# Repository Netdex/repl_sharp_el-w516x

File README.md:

# repl_sharp_el-w516x
`This project is a work-in-progress.`

## Overview
repl_sharp_el-w516x is a design for a replacement logic board for the SHARP EL-W516X calculator.

## Design
The goal of this project is to create a more powerful/elegant calculator out of as many components from the original 
calculator as possible.

This design reuses all components of the calculator except the following:
- Solar panel
  - It does not deliver enough power regardless
- Display
  - Connector pitch is too fine, and flex cable is too fragile
  - There are about 100 pins on the connector, and it requires a application-specific driver
  - The display is replaced with the [NHD-C12832A1Z-FSW-FBW-3V3](http://www.newhavendisplay.com/specs/NHD-C12832A1Z-FSW-FBW-3V3.pdf)
- PCB
- Battery
  - The original battery is an LR44 coin cell watch battery, which does not deliver the power required
  - The battery is replaced with a Samsung 3.8V Li-ion battery 

### Key matrix

The original calculator uses a carbon-coated silicone pad with carbon contacts on the PCB. This design uses the exact 
button pad footprint of the original calculator, with copper contacts instead.

The keys are arranged in a matrix, with a serial-in-parallel-out shift register on the rows, and a 
parallel-in-serial-out shift register on the columns. The microcontroller polls row and column pairs to detect 
key presses. Each column has a diode to avoid sinking 3V3 to GND when two buttons in the same row are pressed. 
In the case of multiple keys presed at once, ghosting will occur since diodes are only placed on a column-basis.

### Power delivery

The board is powered by a battery management IC with power path. The IC upregulates the battery voltage to +BATT + 250mV as VCC, 
where +BATT can vary from 3.0V (depleted) to 4.35V (full). An additional LDO regulates VCC to 3V3, which powers the 
microcontroller and other circuitry. The LDO has a dropout voltage of +250mV, which means that the battery will still 
have a bit of power left when it is depleted. The battery management IC actually charges to CV 4.2V, which means it 
will not charge the battery to full capacity (~80-90%).

The board can be charged via USB, which is also used for programming the microcontroller and other data transfer. 
Charging can occur while the device is being used, due to the power path management provided by the battery management 
IC. The battery charging current will automatically be ducked if the system power path draws too much power, to 
maintain system function. 

### uC
An ATMEGA32U4 microcontroller controls the display, input polling via shift registers, and computation. It is 
programmable via USB interface (factory ships with bootloader). ICSP is exposed via pads if required. 

Since the uC is powered by 3V3, an external 8 MHz oscillator provides the clock source.

## BOM
[InteractiveHtmlBom](https://raw.githack.com/Netdex/repl_sharp_el-w516x/master/kicad/bom/ibom.html)

## Pictures
3D Renders

Populated board (still covered in flux)

Front, in enclosure

Back, in enclosure (I need to file down the jagged edges)

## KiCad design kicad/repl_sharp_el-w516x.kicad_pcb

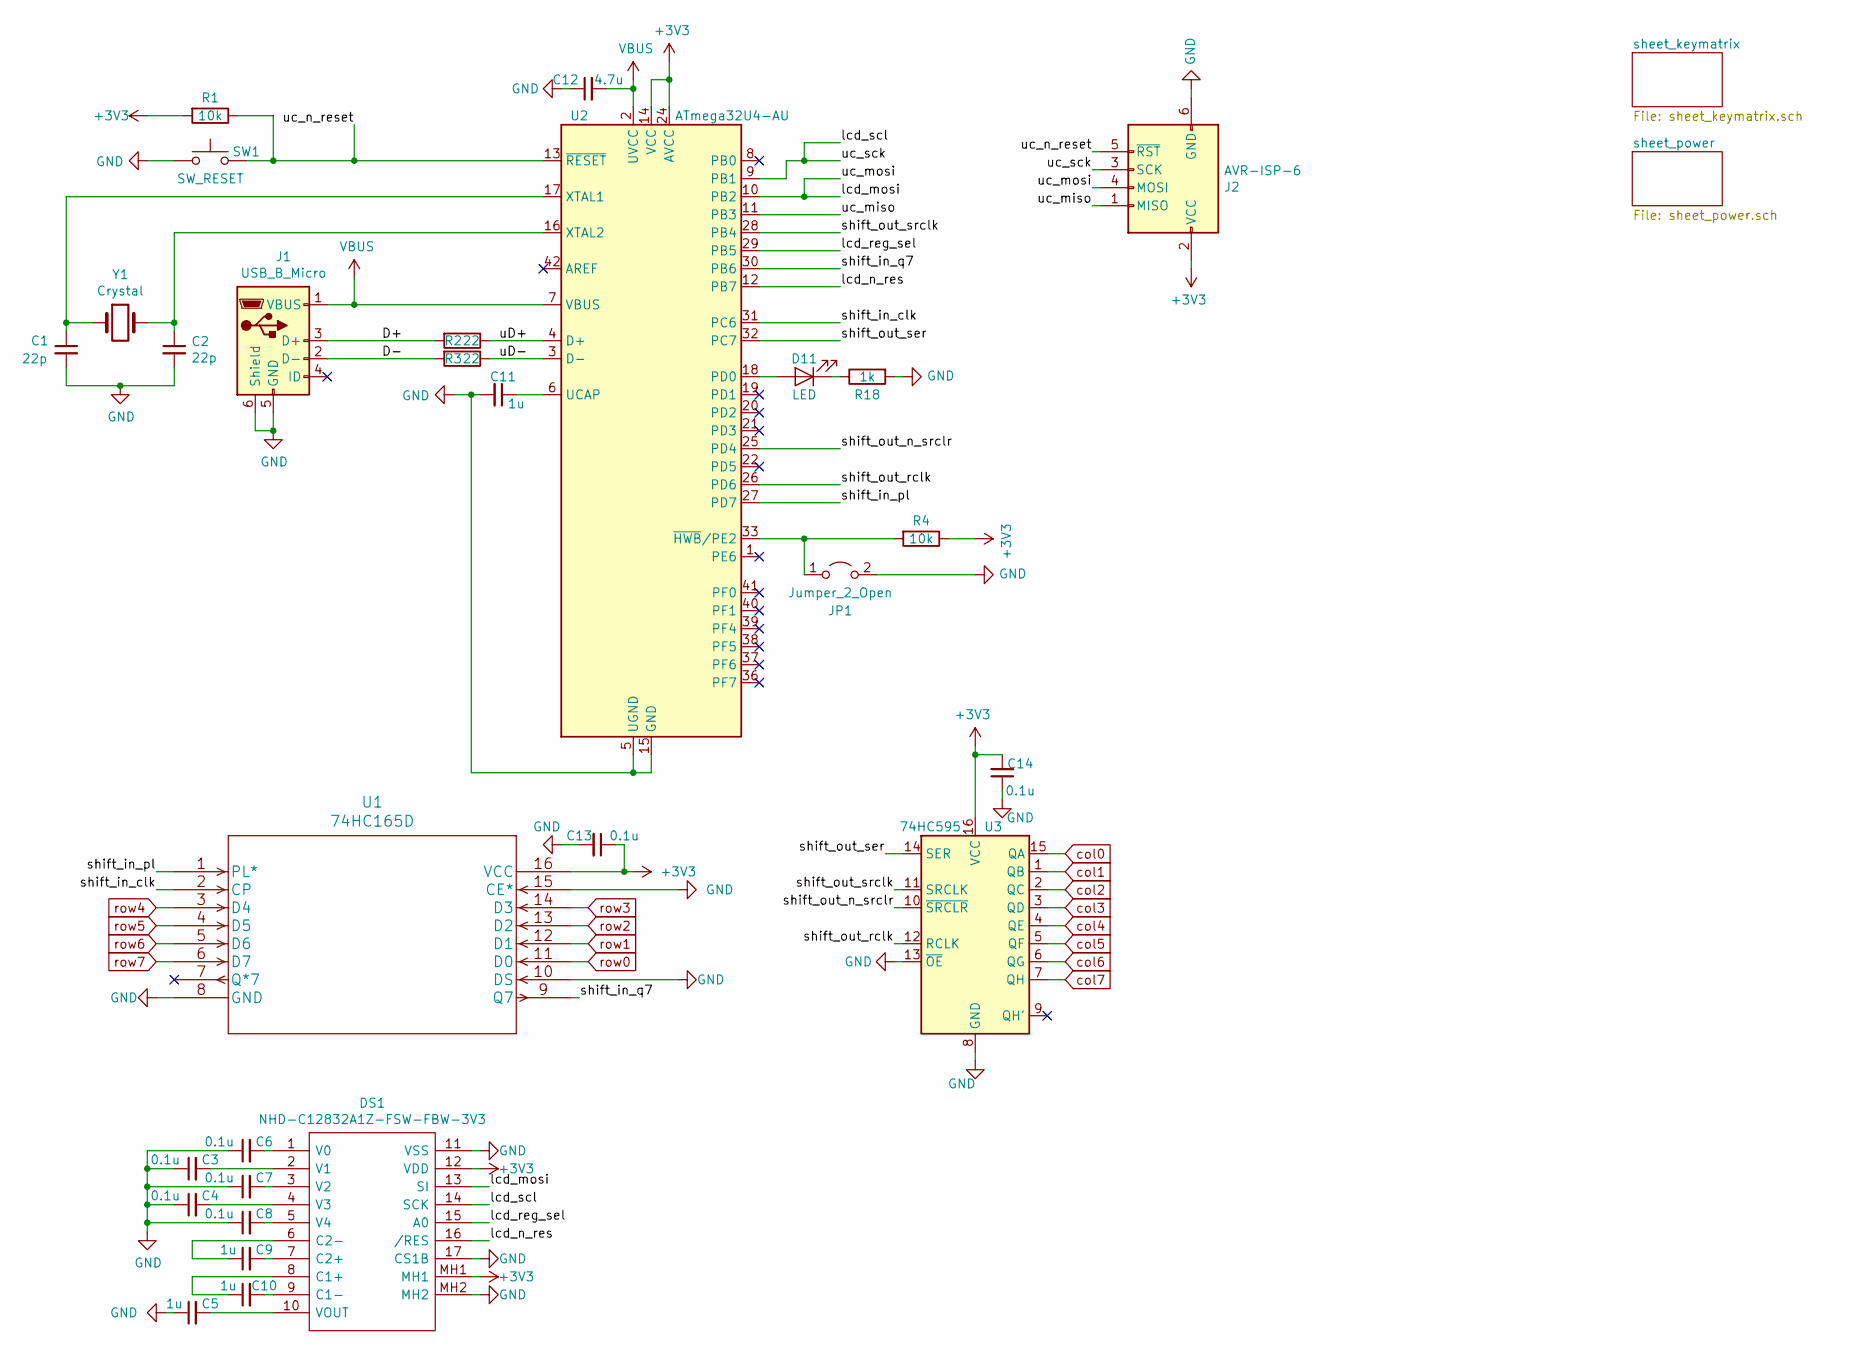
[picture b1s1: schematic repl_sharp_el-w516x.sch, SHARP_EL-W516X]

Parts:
C1, C2: 22p; C_0603_1608Metric_Pad1.05x0.95mm_HandSolder; part_num CC0603JRNPO9BN220; Digi-Key PN 311-1062-1-ND
C3, C4, C6, C7, C8, C13, C14: 0.1u; C_0603_1608Metric_Pad1.05x0.95mm_HandSolder; part_num CL10B104KO8NNNC; Digi-Key PN 1276-1005-1-ND
C5, C9, C10, C11: 1u; C_0603_1608Metric_Pad1.05x0.95mm_HandSolder; part_num CL10A105KP8NNNC; Digi-Key PN 1276-1182-1-ND
C12: 4.7u; C_0603_1608Metric_Pad1.05x0.95mm_HandSolder; part_num CL10A475KQ8NNNC; Digi-Key PN 1276-1045-1-ND
D11: LED; D_0603_1608Metric_Pad1.05x0.95mm_HandSolder; part_num SML-D12U1WT86; Digi-Key PN SML-D12U1WT86CT-ND
DS1: NHD-C12832A1Z-FSW-FBW-3V3; NHDC12832A1ZFSWFBW3V3; Manufacturer_Part_Number NHD-C12832A1Z-FSW-FBW-3V3; Mouser Part Number 763-C12832A1ZFSWFBW3
J1: USB_B_Micro; USB_Micro-B_Amphenol_10103594-0001LF_Horizontal; part_num 10118192-0001LF; Digi-Key PN 609-4613-1-ND
J2: AVR-ISP-6; PinHeader_2x03_P1.27mm_Vertical_SMD
JP1: Jumper_2_Open; SolderJumper-2_P1.3mm_Open_Pad1.0x1.5mm
R1, R4: 10k; R_0603_1608Metric_Pad1.05x0.95mm_HandSolder; part_num RC0603FR-0710KL; Digi-Key PN 311-10.0KHRCT-ND
R2, R3: 22; R_0603_1608Metric_Pad1.05x0.95mm_HandSolder; part_num RC0603FR-0722RL; Digi-Key PN 311-22.0HRCT-ND
R18: 1k; R_0603_1608Metric_Pad1.05x0.95mm_HandSolder; part_num RC0603FR-071KL; Digi-Key PN 311-1.00KHRCT-ND
SW1: SW_RESET; SW_Push_1P1T_NO_6x6mm_H9.5mm; part_num PTS645SM43SMTR92 LFS; Digi-Key PN CKN9112CT-ND
U1: 74HC165D; SOIC-16_3.9x9.9mm_P1.27mm; part_num 74HC165D\\,652; Digi-Key PN 1727-3782-ND
U2: ATmega32U4-AU; TQFP-44_10x10mm_P0.8mm; part_num ATMEGA32U4-AUR; Digi-Key PN ATMEGA32U4-AURCT-ND
U3: 74HC595; SOIC-16_3.9x9.9mm_P1.27mm; part_num SN74HC595DR; Digi-Key PN 296-14857-1-ND
Y1: Crystal; Crystal_SMD_5032-2Pin_5.0x3.2mm; part_num ECS-80-18-30-JGN-TR; Digi-Key PN XC2103CT-ND

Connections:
+3V3: C13.1, C14.2, DS1.12 (VDD), DS1.MH1, J2.2 (VCC), R1.2, R4.1, U1.16 (VCC), U2.14 (VCC), U2.24 (AVCC), U2.34 (VCC), U2.44 (AVCC), U3.16 (VCC); also elsewhere on the board
/D+: J1.3 (D+), R2.2
/D-: J1.2 (D-), R3.2
/lcd_mosi: DS1.13 (SI), J2.4 (MOSI), U2.10 (PB2)
/lcd_n_res: DS1.16 (/RES), U2.12 (PB7)
/lcd_reg_sel: DS1.15 (A0), U2.29 (PB5)
/lcd_scl: DS1.14 (SCK), J2.3 (SCK), U2.9 (PB1)
/shift_in_clk: U1.2 (CP), U2.31 (PC6)
/shift_in_pl: U1.1 (PL*), U2.27 (PD7)
/shift_in_q7: U1.9 (Q7), U2.30 (PB6)
/shift_out_n_srclr: U2.25 (PD4), U3.10 (~SRCLR)
/shift_out_rclk: U2.26 (PD6), U3.12 (RCLK)
/shift_out_ser: U2.32 (PC7), U3.14 (SER)
/shift_out_srclk: U2.28 (PB4), U3.11 (SRCLK)
/uD+: R2.1, U2.4 (D+)
/uD-: R3.1, U2.3 (D-)
/uc_miso: J2.1 (MISO), U2.11 (PB3)
/uc_n_reset: J2.5 (~RST), R1.1, SW1.2, U2.13 (~RESET)
GND: C1.2, C2.2, C3.1, C4.1, C5.1, C6.1, C7.1, C8.1, C11.2, C12.1, C13.2, C14.1, DS1.11 (VSS), DS1.17 (CS1B), DS1.MH2, J1.5 (GND), J1.6 (Shield), J2.6 (GND), JP1.2 (B), R18.2, SW1.1, U1.8 (GND), U1.10 (DS), U1.15 (CE*), U2.5 (UGND), U2.15 (GND), U2.23 (GND), U2.35 (GND), U2.43 (GND), U3.8 (GND), U3.13 (~OE); also elsewhere on the board
unnamed: C1.1, U2.17 (XTAL1), Y1.1
unnamed: C2.1, U2.16 (XTAL2), Y1.2
unnamed: C3.2, DS1.2 (V1)
unnamed: C4.2, DS1.4 (V3)
unnamed: C5.2, DS1.10 (VOUT)
unnamed: C6.2, DS1.1 (V0)
unnamed: C7.2, DS1.3 (V2)
unnamed: C8.2, DS1.5 (V4)
unnamed: C9.1, DS1.6 (C2-)
unnamed: C9.2, DS1.7 (C2+)
unnamed: C10.1, DS1.8 (C1+)
unnamed: C10.2, DS1.9 (C1-)
unnamed: C11.1, U2.6 (UCAP)
unnamed: D11.1 (K), R18.1
unnamed: D11.2 (A), U2.18 (PD0)
unnamed: JP1.1 (A), R4.2, U2.33 (~HWB~/PE2)
VBUS: C12.2, J1.1 (VBUS), U2.2 (UVCC), U2.7 (VBUS); also elsewhere on the board
col0: U3.15 (QA); also elsewhere on the board
col1: U3.1 (QB); also elsewhere on the board
col2: U3.2 (QC); also elsewhere on the board
col3: U3.3 (QD); also elsewhere on the board
col4: U3.4 (QE); also elsewhere on the board
col5: U3.5 (QF); also elsewhere on the board
col6: U3.6 (QG); also elsewhere on the board
col7: U3.7 (QH); also elsewhere on the board
row0: U1.11 (D0); also elsewhere on the board
row1: U1.12 (D1); also elsewhere on the board
row2: U1.13 (D2); also elsewhere on the board
row3: U1.14 (D3); also elsewhere on the board
row4: U1.3 (D4); also elsewhere on the board
row5: U1.4 (D5); also elsewhere on the board
row6: U1.5 (D6); also elsewhere on the board
row7: U1.6 (D7); also elsewhere on the board

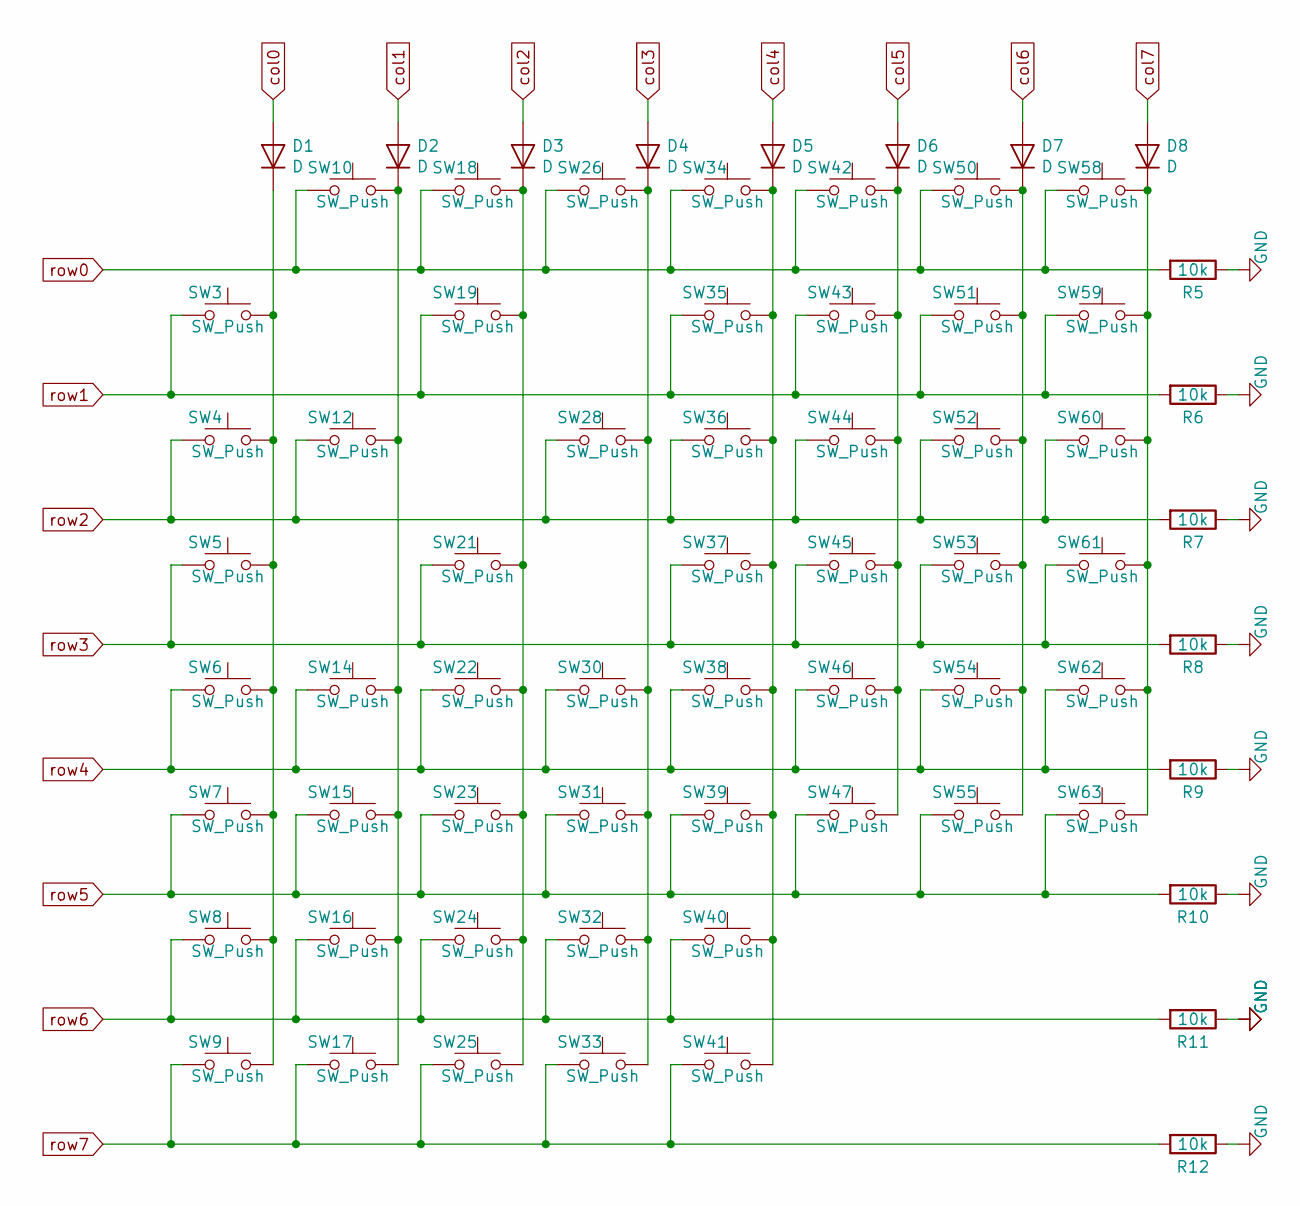
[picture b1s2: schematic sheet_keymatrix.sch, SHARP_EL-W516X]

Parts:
D1, D2, D3, D4, D5, D6, D7, D8: D; D_0603_1608Metric_Pad1.05x0.95mm_HandSolder; part_num TS4148C RZG; Digi-Key PN TS4148CRZGCT-ND
R5, R6, R7, R8, R9, R10, R11, R12: 10k; R_0603_1608Metric_Pad1.05x0.95mm_HandSolder; part_num RC0603FR-0710KL; Digi-Key PN 311-10.0KHRCT-ND
SW3, SW4, SW5, SW10, SW18, SW19, SW21, SW26, SW34, SW35, SW36, SW37: SW_Push; btn_rect
SW6, SW7, SW8, SW9, SW14, SW15, SW16, SW17, SW22, SW23, SW24, SW25, SW30, SW31, SW32, SW33, SW38, SW39, SW40, SW41, SW42, SW43, SW44, SW45, SW46, SW47, SW50, SW51, SW52, SW53, SW54, SW55, SW58, SW59, SW60, SW61, SW62, SW63: SW_Push; btn_circular
SW12, SW28: SW_Push; btn_long_rect

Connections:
GND: R5.1, R6.1, R7.1, R8.1, R9.1, R10.1, R11.1, R12.1; also elsewhere on the board
unnamed: D1.1 (K), SW3.2, SW4.2, SW5.2, SW6.2, SW7.2, SW8.2, SW9.2
unnamed: D2.1 (K), SW10.2, SW12.2, SW14.2, SW15.2, SW16.2, SW17.2
unnamed: D3.1 (K), SW18.2, SW19.2, SW21.2, SW22.2, SW23.2, SW24.2, SW25.2
unnamed: D4.1 (K), SW26.2, SW28.2, SW30.2, SW31.2, SW32.2, SW33.2
unnamed: D5.1 (K), SW34.2, SW35.2, SW36.2, SW37.2, SW38.2, SW39.2, SW40.2, SW41.2
unnamed: D6.1 (K), SW42.2, SW43.2, SW44.2, SW45.2, SW46.2, SW47.2
unnamed: D7.1 (K), SW50.2, SW51.2, SW52.2, SW53.2, SW54.2, SW55.2
unnamed: D8.1 (K), SW58.2, SW59.2, SW60.2, SW61.2, SW62.2, SW63.2
col0: D1.2 (A); also elsewhere on the board
col1: D2.2 (A); also elsewhere on the board
col2: D3.2 (A); also elsewhere on the board
col3: D4.2 (A); also elsewhere on the board
col4: D5.2 (A); also elsewhere on the board
col5: D6.2 (A); also elsewhere on the board
col6: D7.2 (A); also elsewhere on the board
col7: D8.2 (A); also elsewhere on the board
row0: R5.2, SW10.1, SW18.1, SW26.1, SW34.1, SW42.1, SW50.1, SW58.1; also elsewhere on the board
row1: R6.2, SW3.1, SW19.1, SW35.1, SW43.1, SW51.1, SW59.1; also elsewhere on the board
row2: R7.2, SW4.1, SW12.1, SW28.1, SW36.1, SW44.1, SW52.1, SW60.1; also elsewhere on the board
row3: R8.2, SW5.1, SW21.1, SW37.1, SW45.1, SW53.1, SW61.1; also elsewhere on the board
row4: R9.2, SW6.1, SW14.1, SW22.1, SW30.1, SW38.1, SW46.1, SW54.1, SW62.1; also elsewhere on the board
row5: R10.2, SW7.1, SW15.1, SW23.1, SW31.1, SW39.1, SW47.1, SW55.1, SW63.1; also elsewhere on the board
row6: R11.2, SW8.1, SW16.1, SW24.1, SW32.1, SW40.1; also elsewhere on the board
row7: R12.2, SW9.1, SW17.1, SW25.1, SW33.1, SW41.1; also elsewhere on the board

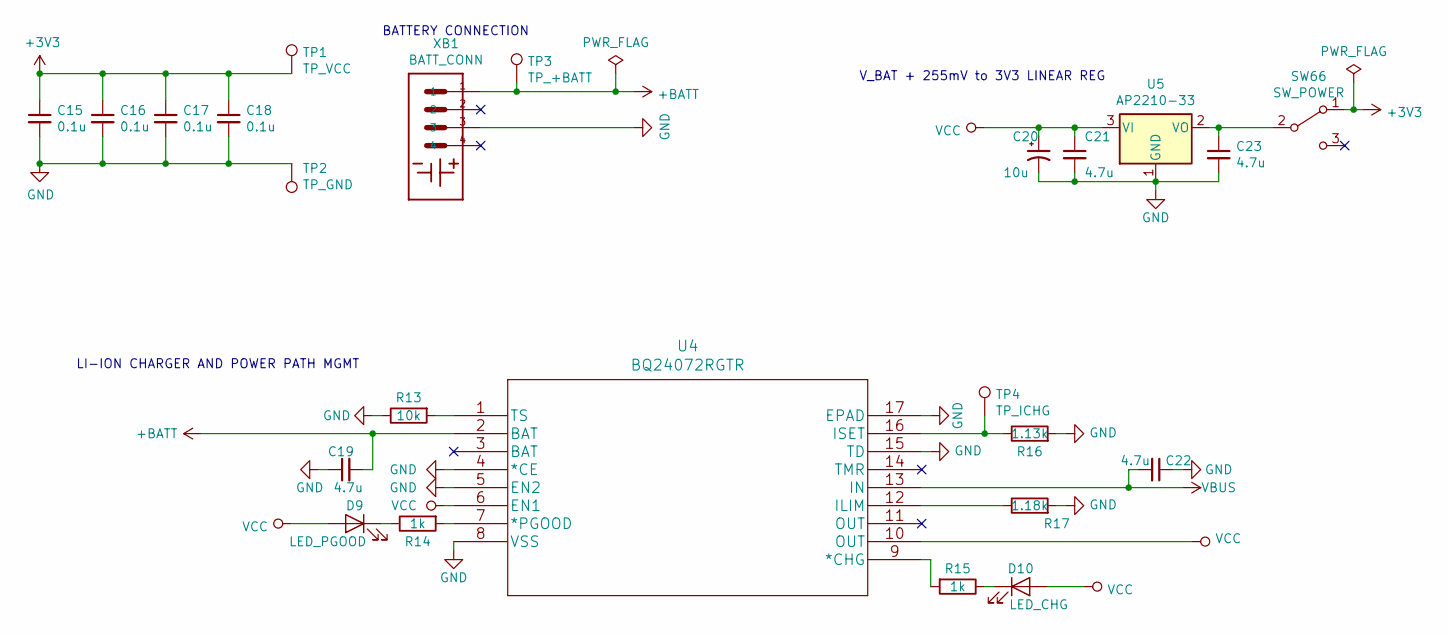
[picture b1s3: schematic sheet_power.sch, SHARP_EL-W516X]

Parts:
C15, C16, C17, C18: 0.1u; C_0603_1608Metric_Pad1.05x0.95mm_HandSolder; part_num CL10B104KO8NNNC; Digi-Key PN 1276-1005-1-ND
C19, C21, C22, C23: 4.7u; C_0603_1608Metric_Pad1.05x0.95mm_HandSolder; part_num CL10A475KQ8NNNC; Digi-Key PN 1276-1045-1-ND
C20: 10u; CP_Elec_4x5.3; part_num UZR1C100MCL1GB; Digi-Key PN 493-10106-1-ND
D9: LED_PGOOD; LED_0603_1608Metric_Pad1.05x0.95mm_HandSolder; part_num SML-D12U1WT86; Digi-Key PN SML-D12U1WT86CT-ND
D10: LED_CHG; LED_0603_1608Metric_Pad1.05x0.95mm_HandSolder; part_num SML-D12U1WT86; Digi-Key PN SML-D12U1WT86CT-ND
R13: 10k; R_0603_1608Metric_Pad1.05x0.95mm_HandSolder; part_num RC0603FR-0710KL; Digi-Key PN 311-10.0KHRCT-ND
R14, R15: 1k; R_0603_1608Metric_Pad1.05x0.95mm_HandSolder; part_num RC0603FR-071KL; Digi-Key PN 311-1.00KHRCT-ND
R16: 1.13k; R_0603_1608Metric_Pad1.05x0.95mm_HandSolder; part_num RC0603FR-071K13L; Digi-Key PN 311-1.13KHRCT-ND
R17: 1.18k; R_0603_1608Metric_Pad1.05x0.95mm_HandSolder; part_num RC0603FR-071K18L; Digi-Key PN 311-1.18KHRCT-ND
SW66: SW_POWER; SW_SPDT_CK-JS102011SAQN; part_num JS102011SAQN; Digi-Key PN 401-1999-1-ND
TP1: TP_VCC; TestPoint_Pad_1.0x1.0mm
TP2: TP_GND; TestPoint_Pad_1.0x1.0mm
TP3: TP_+BATT; TestPoint_Pad_1.0x1.0mm
TP4: TP_ICHG; TestPoint_Pad_1.0x1.0mm
U4: BQ24072RGTR; part_num BQ24072RGTR; Digi-Key PN 296-38871-1-ND
U5: AP2210-33; SOT-23; part_num AP2210N-3.3TRG1; Digi-Key PN AP2210N-3.3TRG1DICT-ND
XB1: BATT_CONN; BAT_009155004541006; part_num 009155004541006; Digi-Key PN 478-5452-1-ND

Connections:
+3V3: C15.1, C16.1, C17.1, C18.1, SW66.1 (A), TP1.1; also elsewhere on the board
+BATT: C19.2, TP3.1, U4.2 (BAT), XB1.1
GND: C15.2, C16.2, C17.2, C18.2, C19.1, C20.2, C21.2, C22.1, C23.2, R13.1, R16.2, R17.2, TP2.1, U4.4 (*CE), U4.5 (EN2), U4.8 (VSS), U4.15 (TD), U4.17 (EPAD), U5.1 (GND), XB1.3; also elsewhere on the board
unnamed: C23.1, SW66.2 (B), U5.2 (VO)
unnamed: D9.1 (K), R14.1
unnamed: D10.1 (K), R15.1
unnamed: R13.2, U4.1 (TS)
unnamed: R14.2, U4.7 (*PGOOD)
unnamed: R15.2, U4.9 (*CHG)
unnamed: R16.1, TP4.1, U4.16 (ISET)
unnamed: R17.1, U4.12 (ILIM)
VBUS: C22.2, U4.13 (IN); also elsewhere on the board
VCC: C20.1, C21.1, D9.2 (A), D10.2 (A), U4.6 (EN1), U4.10 (OUT), U5.3 (VI)

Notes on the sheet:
V_BAT + 255mV to 3V3 LINEAR REG
BATTERY CONNECTION
LI-ION CHARGER AND POWER PATH MGMT

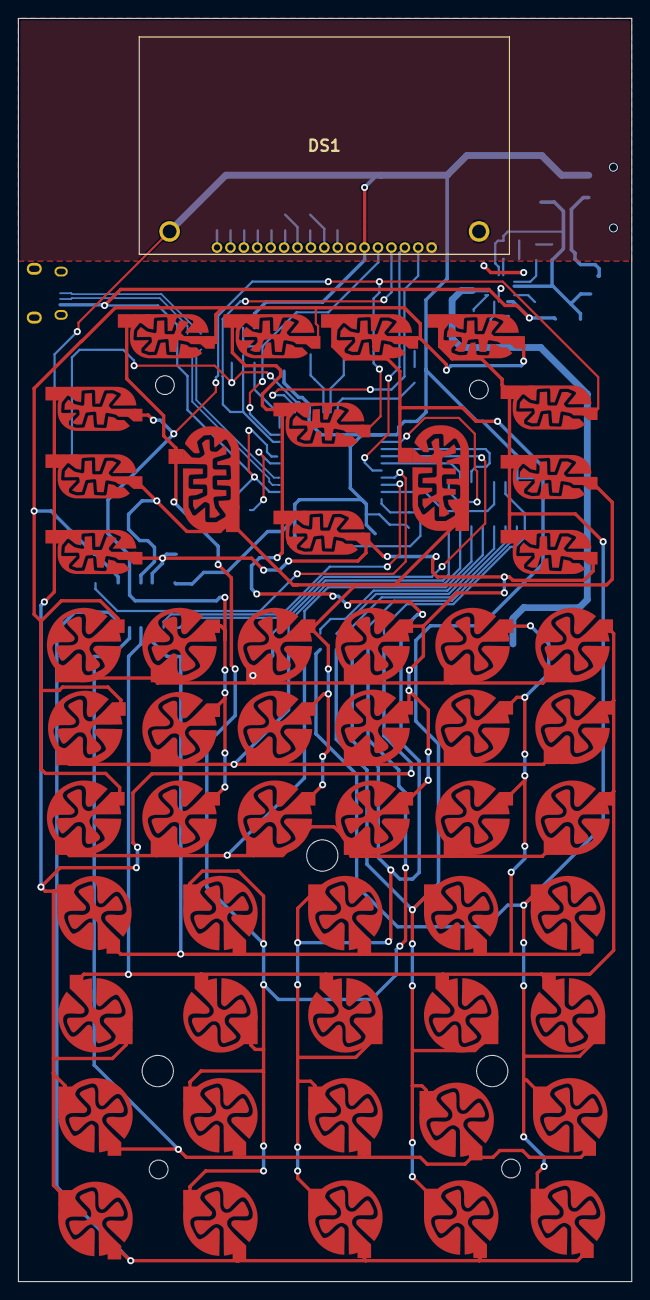
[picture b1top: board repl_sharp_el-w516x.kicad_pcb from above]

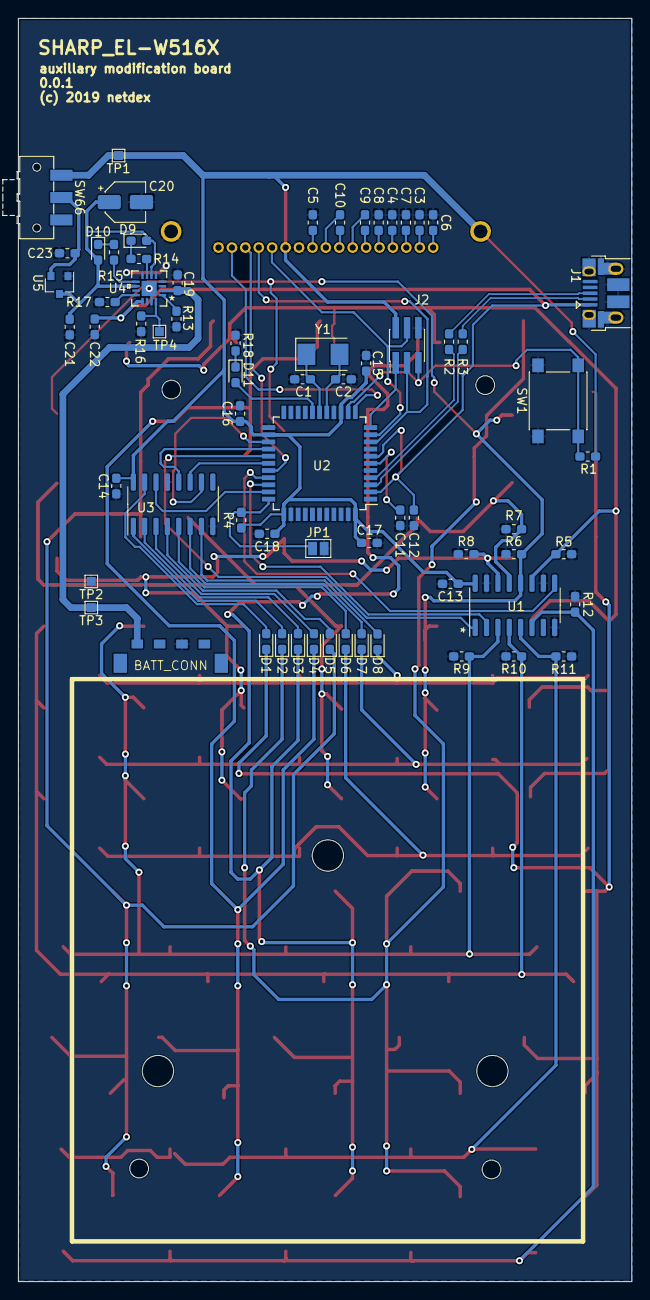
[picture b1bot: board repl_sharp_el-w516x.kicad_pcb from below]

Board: 2 copper layers, 68.6 x 141.2 mm, 121 parts (68 on the bottom side), 70 nets.

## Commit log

2019-06-06 pcb: initial design barring supply power and display
2019-06-09 docs: create readme
2019-06-17 docs: update readme
2019-06-17 kicad: update schematic and pcb
2019-06-30 kicad: completed partial layout
2019-07-05 kicad: finalize design
2019-07-07 kicad: design after production
2019-07-07 kicad: finalize device BOM
2019-07-08 kicad: fix virtual component
2019-07-19 firmware: first implementation with symbolic math

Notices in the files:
kicad/repl_sharp_el-w516x.kicad_pcb:
(c) 2019 netdex
parts and their libraries:
Copyright 2016 Accelerated Designs. All rights reserved.
